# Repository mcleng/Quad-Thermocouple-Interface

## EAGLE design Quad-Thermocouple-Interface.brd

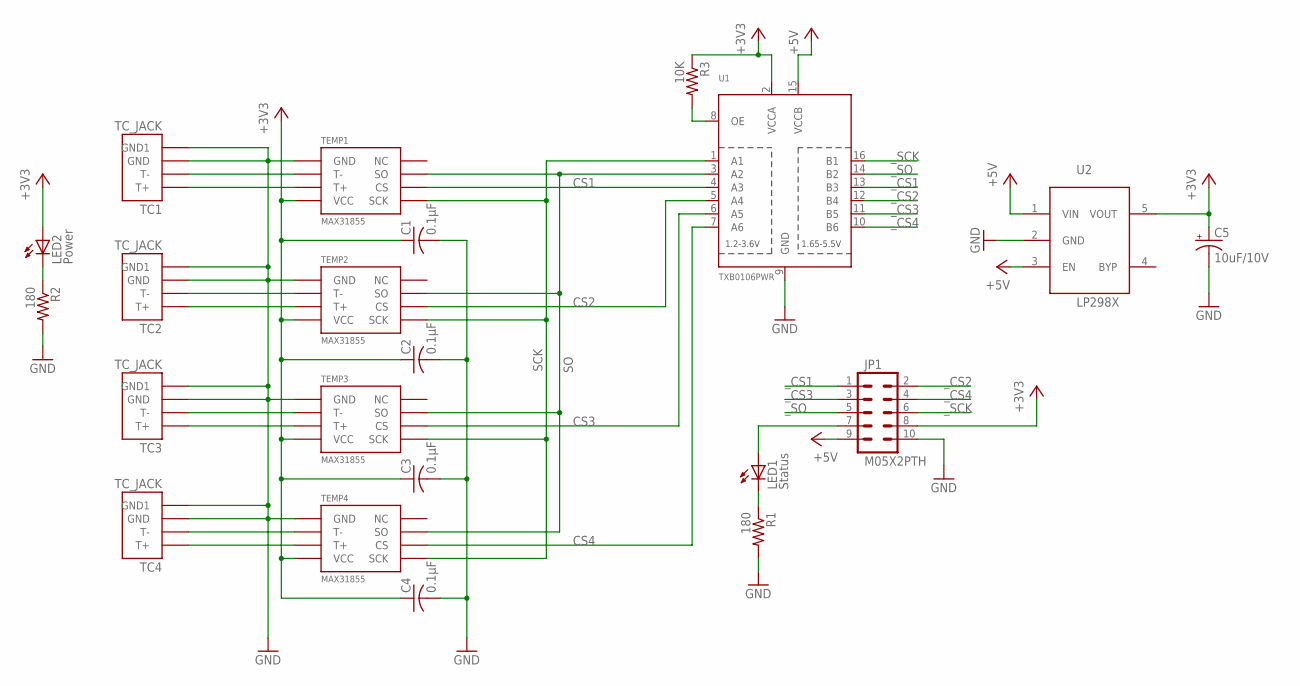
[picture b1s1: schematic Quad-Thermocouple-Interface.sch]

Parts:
C1, C2, C3, C4: 0.1µF; C0603
C5: 10uF/10V; A/3216-18R
JP1: M05X2PTH; AVR_ICSP
LED1: Status; CHIPLED_0805
LED2: Power; CHIPLED_0805
R1, R2: 180; R0603
R3: 10K; R0603
TC1, TC2, TC3, TC4: TC_JACK
TEMP1, TEMP2, TEMP3, TEMP4: MAX31855; SOIC-8
U1: TXB0106PWR; TSSOP16
U2: LP298XS; SOT23-5L

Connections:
+3V3: C1.1, C2.1, C3.1, C4.1, C5.+, JP1.8, LED2.A, R3.1, TEMP1.VCC, TEMP2.VCC, TEMP3.VCC, TEMP4.VCC, U1.2 (VCCA), U2.5 (VOUT)
+5V: JP1.9, U1.15 (VCCB), U2.1 (VIN), U2.3 (EN)
CS1: TEMP1.CS, U1.4 (A3)
CS2: TEMP2.CS, U1.5 (A4)
CS3: TEMP3.CS, U1.6 (A5)
CS4: TEMP4.CS, U1.7 (A6)
GND: C1.2, C2.2, C3.2, C4.2, C5.-, JP1.10, R1.2, R2.2, TC1.P$1 (GND), TC1.P$2 (GND1), TC2.P$1 (GND), TC2.P$2 (GND1), TC3.P$1 (GND), TC3.P$2 (GND1), TC4.P$1 (GND), TC4.P$2 (GND1), TEMP1.GND, TEMP2.GND, TEMP3.GND, TEMP4.GND, U1.9 (GND), U2.2 (GND)
LED1: JP1.7, LED1.A
unnamed: R3.2, U1.8 (OE)
unnamed: LED1.C, R1.1
unnamed: LED2.C, R2.1
SCK: TEMP1.SCK, TEMP2.SCK, TEMP3.SCK, TEMP4.SCK, U1.1 (A1)
SO: TEMP1.SO, TEMP2.SO, TEMP3.SO, TEMP4.SO, U1.3 (A2)
T1: TC1.T+, TEMP1.T+
T1-: TC1.T-, TEMP1.T-
T2: TC2.T+, TEMP2.T+
T2-: TC2.T-, TEMP2.T-
T3: TC3.T+, TEMP3.T+
T3-: TC3.T-, TEMP3.T-
T4: TC4.T+, TEMP4.T+
T4-: TC4.T-, TEMP4.T-
_CS1: JP1.1, U1.13 (B3)
_CS2: JP1.2, U1.12 (B4)
_CS3: JP1.3, U1.11 (B5)
_CS4: JP1.4, U1.10 (B6)
_SCK: JP1.6, U1.16 (B1)
_SO: JP1.5, U1.14 (B2)

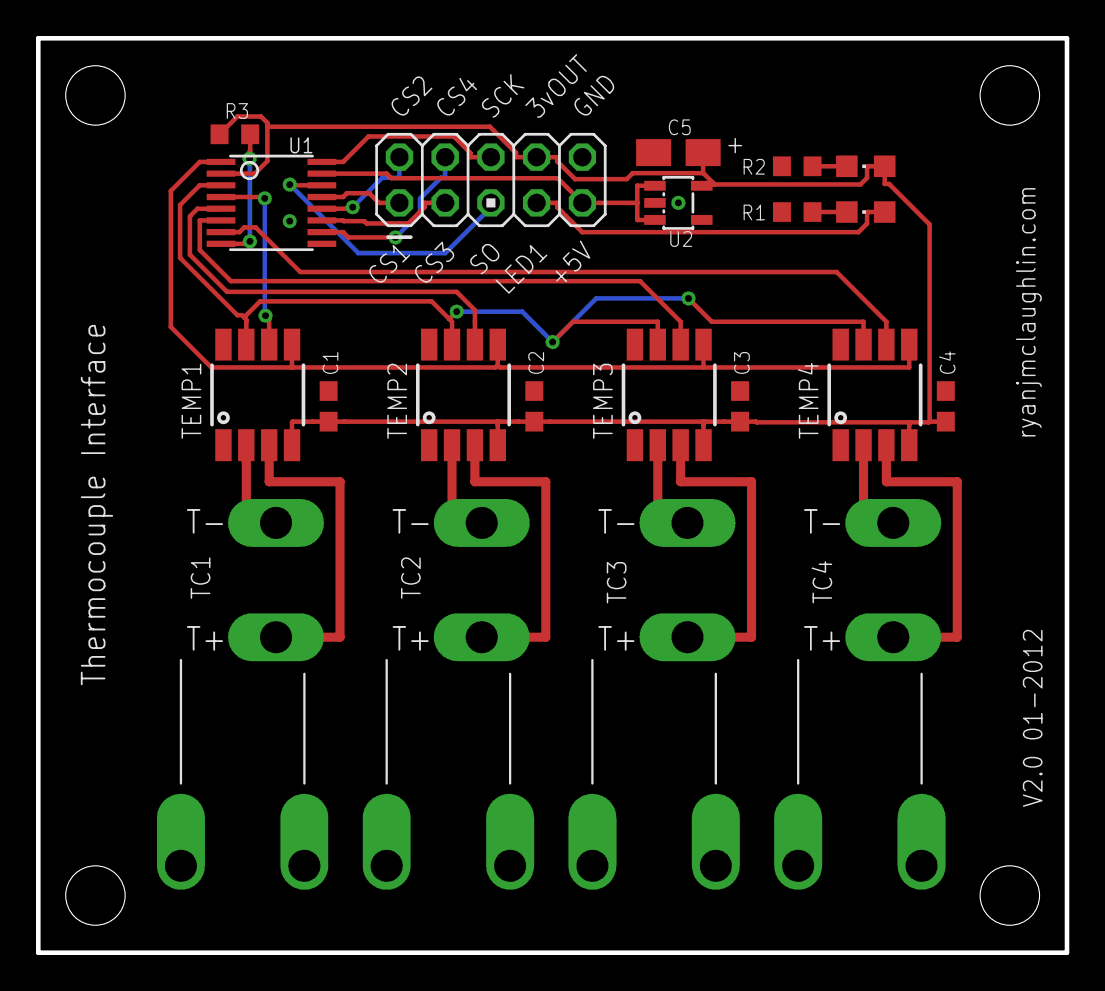
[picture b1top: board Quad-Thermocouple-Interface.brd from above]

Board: 2 copper layers, 57.1 x 50.8 mm, 25 parts (0 on the bottom side), 27 nets.

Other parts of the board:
U$1, U$2, U$3, U$4: STAND-OFF

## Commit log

2012-01-30 Initial release for git v1.4
2012-02-01 Updated with level shifter and power supply for MAX31855, rev to v2.0
